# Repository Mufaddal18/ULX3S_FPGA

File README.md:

# ULX3S_FPGA
 University digital Logic Learning Xtensible board with SDRAM

ULX3S FPGA Board, open-source innovation designed to empower education, research, and a myriad of other projects. Standing 8 layer board with the form size of 57x53 mm.

Some of the feature of board are - 

🔹 Affordable Excellence: The ULX3S is low-cost FPGA board packed with all the essential features.

🔹 Versatile and Feature-Packed:  It's an all-in-one solution with an HDMI display, buttons, storage, WiFi connectivity, and compatible connectors. It's designed to be the go-to tool 
   for research, education, and makerspaces.

🔹 Rich Connectivity: With a comprehensive set of chips and connectivity options, including SDRAM, USB, PS/2, SDCARD, Digital Video, FLASH, RTC, I2C, Display, AUDIO, ADC, and more, the 
   ULX3S is a versatile canvas for open-source projects.

At last I would like to thank Emard for making this project open source. 

Your ideas, feedback, and collaboration are not just welcome; they're essential.

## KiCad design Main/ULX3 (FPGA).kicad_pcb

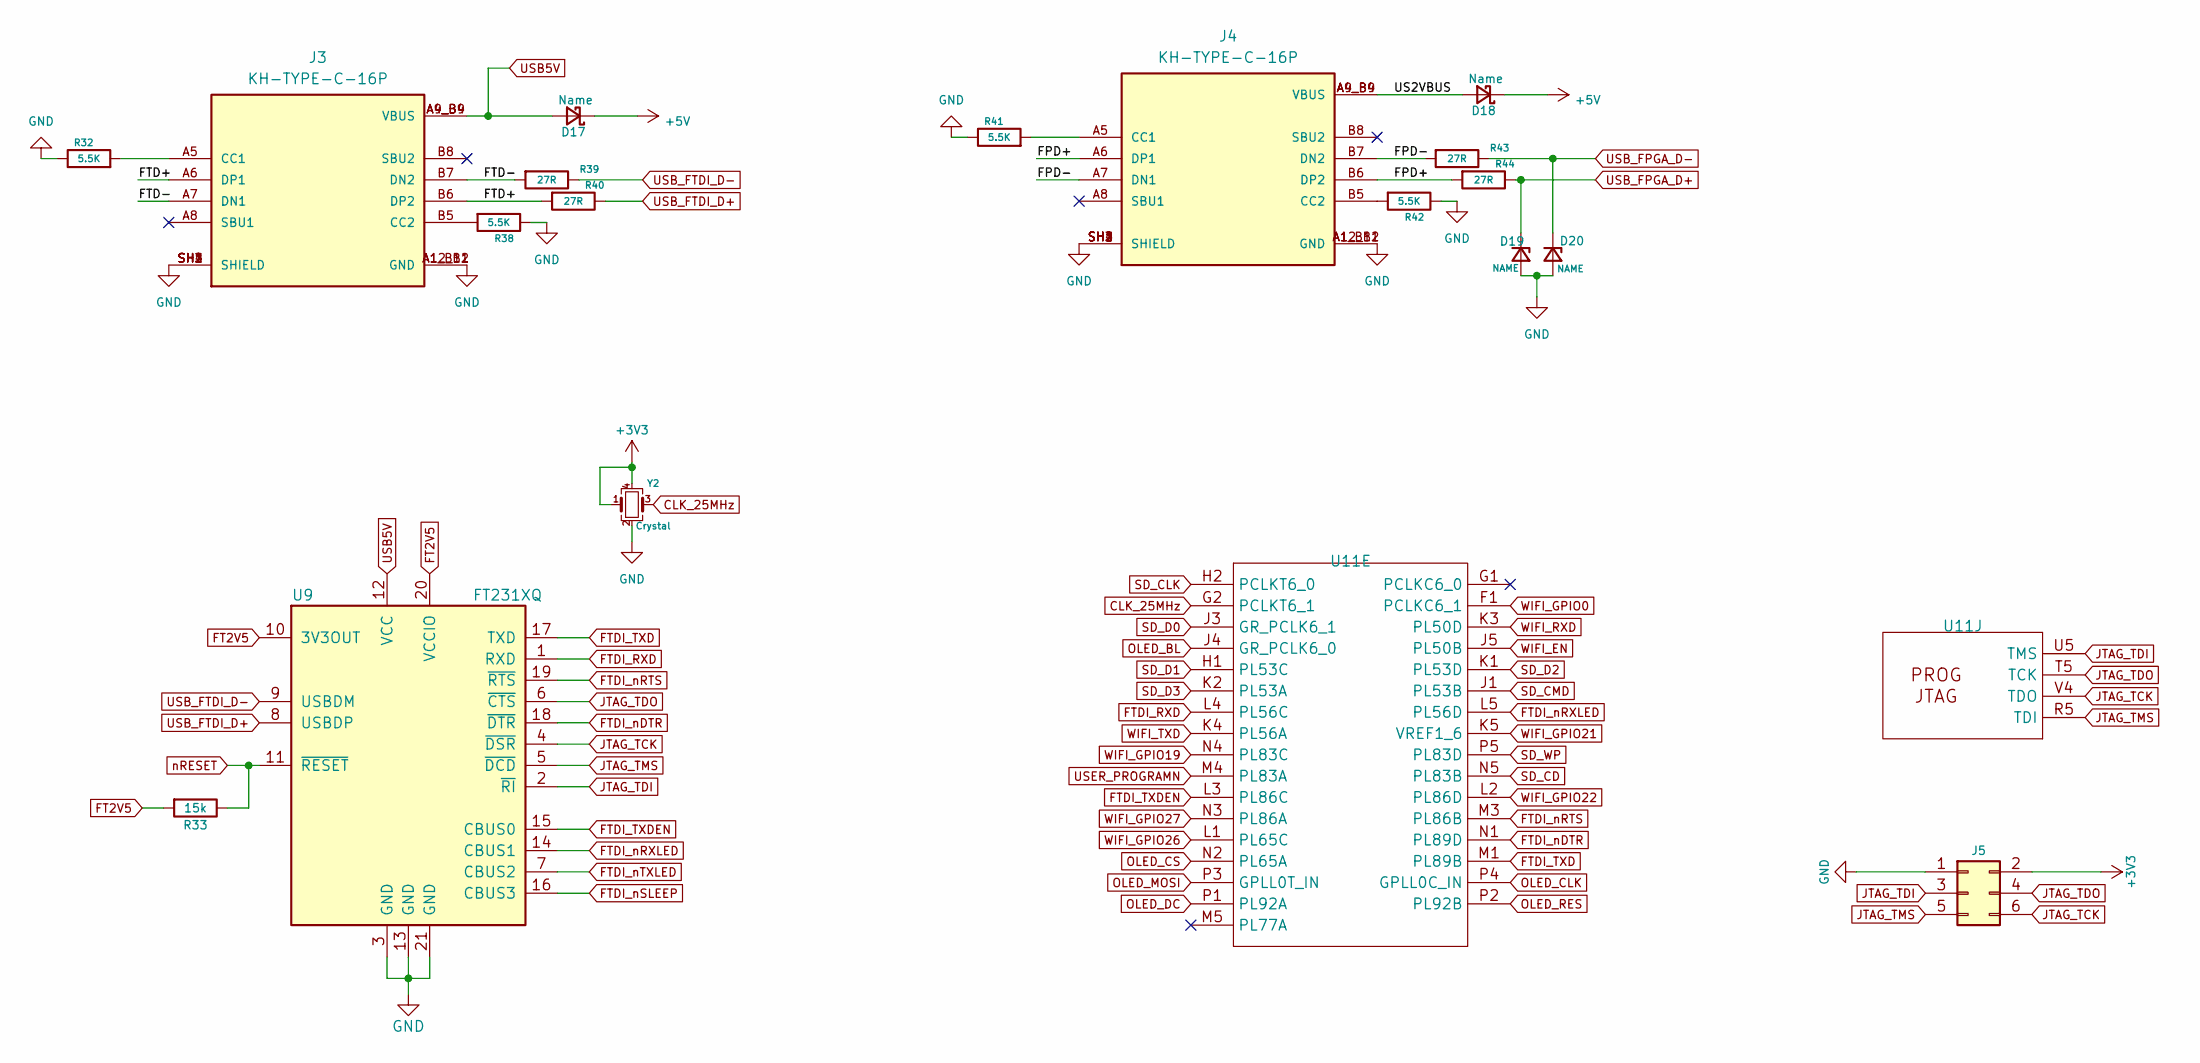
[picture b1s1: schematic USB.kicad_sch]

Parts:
D17, D18: Name; D_0402_1005Metric
D19, D20: NAME; D_0402_1005Metric
J3, J4: KH-TYPE-C-16P; KINGHELM_KH-TYPE-C-16P; PARTREV A0
J5: PinHeader_2x03_P2.54mm_Vertical
R32, R38, R41, R42: 5.5K; R_0402_1005Metric; MPN AC0603JR-0727RL; Mouser 603-AC0603JR-0727RL
R33: 15k; R_0402_1005Metric; MPN RC0603FR-0715KL; Mouser 603-AC0603FR-1015KL
R39, R43: 27R; R_0402_1005Metric; MPN AC0603JR-0727RL; Mouser 603-AC0603JR-0727RL
R40, R44: 27R; R_0402_1005Metric; MPN AC0603JR-0727RL
U9: FT231XQ; MPN FT231XQ; Mouser 895-FT231XQ-R
U11: Latice_LEF5U_FPGA_BGA-381
Y2: Crystal; Crystal_SMD_3225-4Pin_3.2x2.5mm

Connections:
+3V3: J5.2, Y2.1, Y2.4; also elsewhere on the board
+5V: D17.1 (K), D18.1 (K); also elsewhere on the board
/USB/ANT_433MHz: U11.G1 (PCLKC6_0)
/USB/FPD+: J4.A6 (DP1), J4.B6 (DP2), R44.2
/USB/FPD-: J4.A7 (DN1), J4.B7 (DN2), R43.2
/USB/FTD+: J3.A6 (DP1), J3.B6 (DP2), R40.2
/USB/FTD-: J3.A7 (DN1), J3.B7 (DN2), R39.2
/USB/US2VBUS: D18.2 (A), J4.A4_B9 (VBUS), J4.A9_B4 (VBUS)
CLK_25MHz: U11.G2 (PCLKT6_1), Y2.3
FT2V5: R33.2, U9.10 (3V3OUT), U9.20 (VCCIO); also elsewhere on the board
FTDI_RXD: U9.1 (RXD), U11.L4 (PL56C)
FTDI_TXD: U9.17 (TXD), U11.M1 (PL89B)
FTDI_TXDEN: U9.15 (CBUS0), U11.L3 (PL86C)
FTDI_nDTR: U9.18 (~DTR), U11.N1 (PL89D)
FTDI_nRTS: U9.19 (~RTS), U11.M3 (PL86B)
FTDI_nRXLED: U9.14 (CBUS1), U11.L5 (PL56D)
FTDI_nSLEEP: U9.16 (CBUS3); also elsewhere on the board
FTDI_nTXLED: U9.7 (CBUS2); also elsewhere on the board
JTAG_TCK: J5.6, U9.4 (~DSR), U11.V4 (TDO); also elsewhere on the board
JTAG_TDI: J5.3, U9.2 (~RI), U11.U5 (TMS); also elsewhere on the board
JTAG_TDO: J5.4, U9.6 (~CTS), U11.T5 (TCK); also elsewhere on the board
JTAG_TMS: J5.5, U9.5 (~DCD), U11.R5 (TDI); also elsewhere on the board
unnamed: J3.A5 (CC1), R32.2
unnamed: J3.B5 (CC2), R38.2
unnamed: J4.A5 (CC1), R41.2
unnamed: J4.B5 (CC2), R42.2
OLED_BL: U11.J4 (GR_PCLK6_0)
OLED_CLK: U11.P4 (GPLL0C_IN)
OLED_CS: U11.N2 (PL65A)
OLED_DC: U11.P1 (PL92A)
OLED_MOSI: U11.P3 (GPLL0T_IN)
OLED_RES: U11.P2 (PL92B)
SD_CD: U11.N5 (PL83B)
SD_CLK: U11.H2 (PCLKT6_0); also elsewhere on the board
SD_CMD: U11.J1 (PL53B); also elsewhere on the board
SD_D0: U11.J3 (GR_PCLK6_1); also elsewhere on the board
SD_D1: U11.H1 (PL53C); also elsewhere on the board
SD_D2: U11.K1 (PL53D); also elsewhere on the board
SD_D3: U11.K2 (PL53A); also elsewhere on the board
SD_WP: U11.P5 (PL83D)
USB5V: D17.2 (A), J3.A4_B9 (VBUS), J3.A9_B4 (VBUS), U9.12 (VCC)
USB_FPGA_D+: D19.1 (K), R44.1; also elsewhere on the board
USB_FPGA_D-: D20.1 (K), R43.1; also elsewhere on the board
USB_FTDI_D+: R40.1, U9.8 (USBDP)
USB_FTDI_D-: R39.1, U9.9 (USBDM)
USER_PROGRAMN: U11.M4 (PL83A); also elsewhere on the board
WIFI_EN: U11.J5 (PL50B); also elsewhere on the board
WIFI_GPIO0: U11.F1 (PCLKC6_1); also elsewhere on the board
WIFI_GPIO19: U11.N4 (PL83C); also elsewhere on the board
WIFI_GPIO21: U11.K5 (VREF1_6); also elsewhere on the board
WIFI_GPIO22: U11.L2 (PL86D); also elsewhere on the board
WIFI_GPIO26: U11.L1 (PL65C); also elsewhere on the board
WIFI_GPIO27: U11.N3 (PL86A); also elsewhere on the board
WIFI_RXD: U11.K3 (PL50D); also elsewhere on the board
WIFI_TXD: U11.K4 (PL56A); also elsewhere on the board
nRESET: R33.1, U9.11 (~RESET)

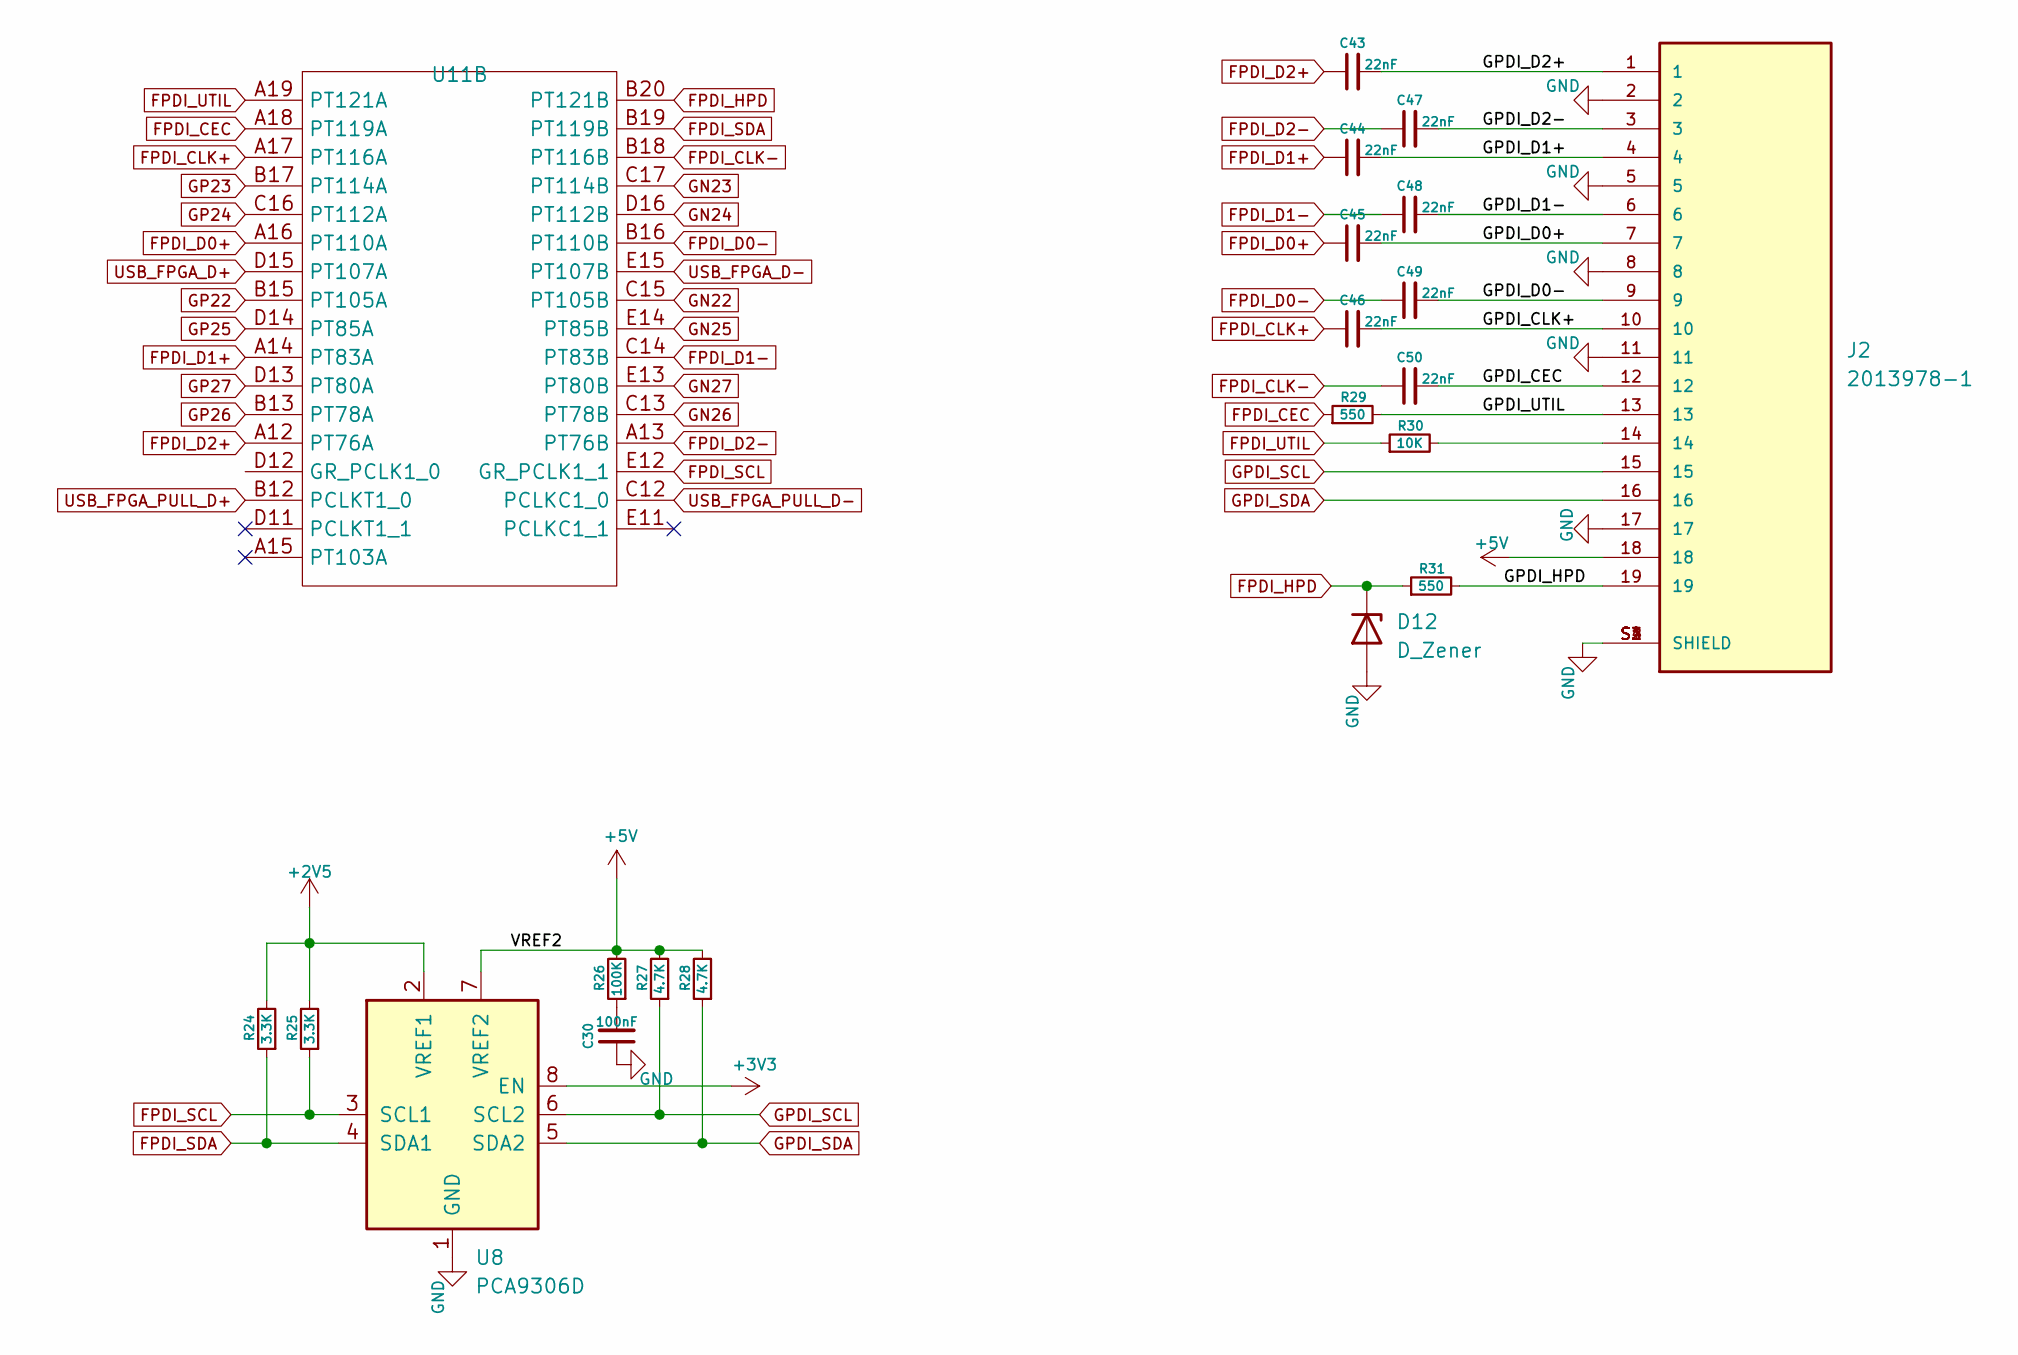
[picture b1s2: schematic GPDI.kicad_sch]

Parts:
C30: 100nF; C_0402_1005Metric
C43, C44, C45, C46, C47, C48, C49, C50: 22nF; C_0402_1005Metric
D12: D_Zener; D_0402_1005Metric
J2: 2013978-1; HDMI-019S
R24, R25: 3.3K; R_0402_1005Metric
R26: 100K; R_0402_1005Metric
R27, R28: 4.7K; R_0402_1005Metric
R29, R31: 550; R_0402_1005Metric
R30: 10K; R_0402_1005Metric
U8: PCA9306D; SO-8_3.9x4.9mm_P1.27mm
U11: Latice_LEF5U_FPGA_BGA-381

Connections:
+2V5: R24.2, R25.2, U8.2 (VREF1); also elsewhere on the board
+3V3: U8.8 (EN); also elsewhere on the board
+5V: J2.18, R26.2, R27.2, R28.2, U8.7 (VREF2); also elsewhere on the board
/GPDI/GPDI_CEC: C50.2, J2.12
/GPDI/GPDI_CLK+: C46.2, J2.10
/GPDI/GPDI_D0+: C45.2, J2.7
/GPDI/GPDI_D0-: C49.2, J2.9
/GPDI/GPDI_D1+: C44.2, J2.4
/GPDI/GPDI_D1-: C48.2, J2.6
/GPDI/GPDI_D2+: C43.2, J2.1
/GPDI/GPDI_D2-: C47.2, J2.3
/GPDI/GPDI_HPD: J2.19, R31.2
/GPDI/GPDI_UTIL: J2.13, R29.2
FPDI_CEC: R29.1, U11.A18 (PT119A)
FPDI_CLK+: C46.1, U11.A17 (PT116A)
FPDI_CLK-: C50.1, U11.B18 (PT116B)
FPDI_D0+: C45.1, U11.A16 (PT110A)
FPDI_D0-: C49.1, U11.B16 (PT110B)
FPDI_D1+: C44.1, U11.A14 (PT83A)
FPDI_D1-: C48.1, U11.C14 (PT83B)
FPDI_D2+: C43.1, U11.A12 (PT76A)
FPDI_D2-: C47.1, U11.A13 (PT76B)
FPDI_HPD: D12.1 (K), R31.1, U11.B20 (PT121B)
FPDI_SCL: R25.1, U8.3 (SCL1), U11.E12 (GR_PCLK1_1); also elsewhere on the board
FPDI_SDA: R24.1, U8.4 (SDA1), U11.B19 (PT119B); also elsewhere on the board
FPDI_UTIL: R30.1, U11.A19 (PT121A)
GN22: U11.C15 (PT105B)
GN23: U11.C17 (PT114B)
GN24: U11.D16 (PT112B)
GN25: U11.E14 (PT85B)
GN26: U11.C13 (PT78B)
GN27: U11.E13 (PT80B)
GP22: U11.B15 (PT105A)
GP23: U11.B17 (PT114A)
GP24: U11.C16 (PT112A)
GP25: U11.D14 (PT85A)
GP26: U11.B13 (PT78A)
GP27: U11.D13 (PT80A)
GPDI_SCL: J2.15, R27.1, U8.6 (SCL2)
GPDI_SDA: J2.16, R28.1, U8.5 (SDA2)
unnamed: C30.2, R26.1
unnamed: J2.14, R30.2
USB_FPGA_D+: U11.D15 (PT107A); also elsewhere on the board
USB_FPGA_D-: U11.E15 (PT107B); also elsewhere on the board
USB_FPGA_PULL_D+: U11.B12 (PCLKT1_0)
USB_FPGA_PULL_D-: U11.C12 (PCLKC1_0)

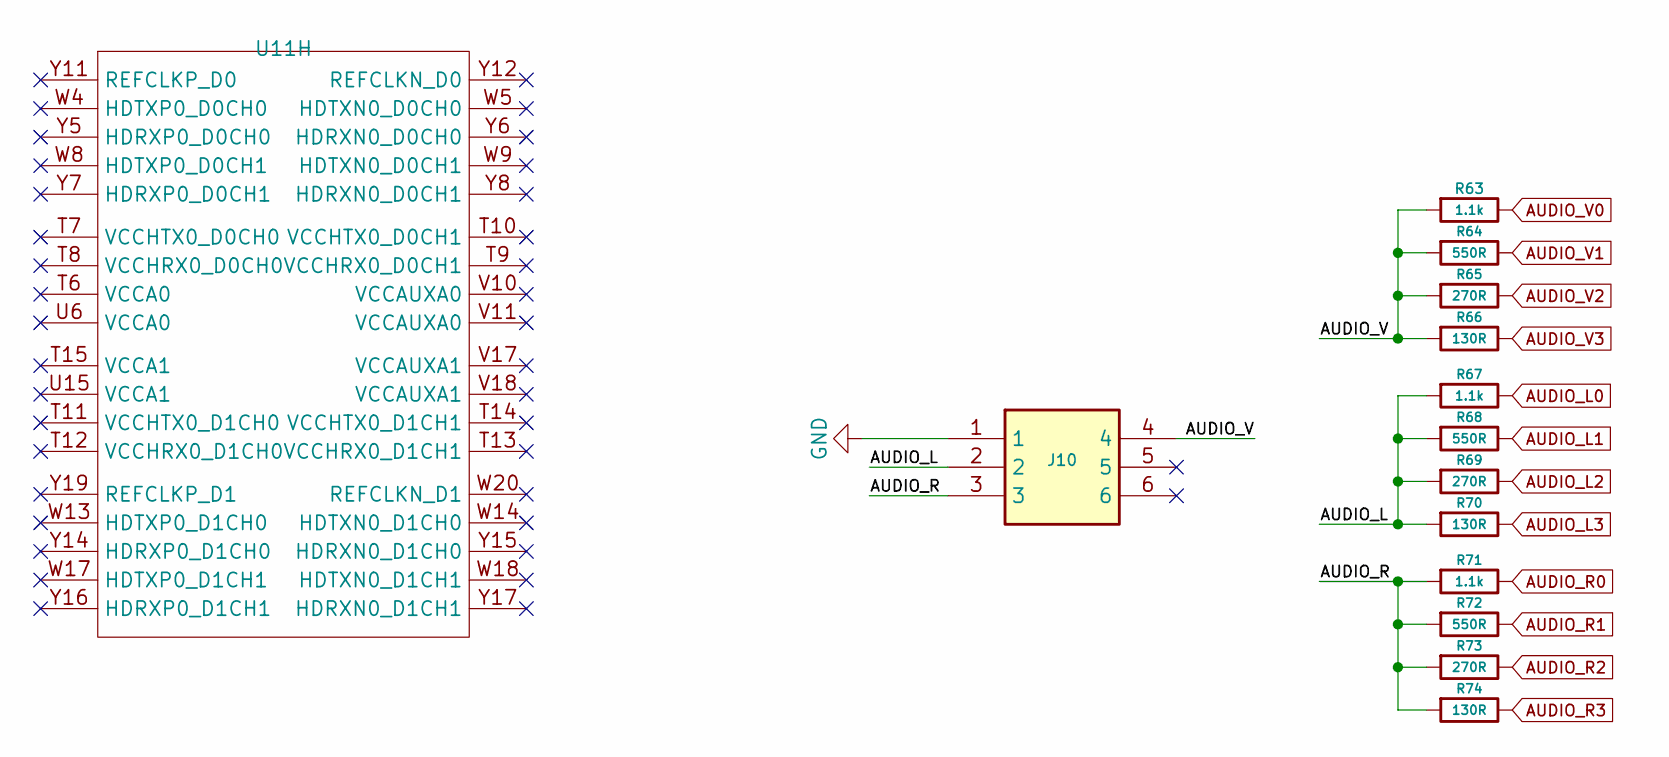
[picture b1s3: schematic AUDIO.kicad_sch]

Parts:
J10: SJ43516SMTTR; Manufacturer_Part_Number SJ-43516-SMT-TR; Mouser Part Number 490-SJ-43516-SMT-TR
R63, R71: 1.1k; R_0402_1005Metric
R64, R72: 550R; R_0402_1005Metric
R65, R73: 270R; R_0402_1005Metric
R66, R74: 130R; R_0402_1005Metric
R67: 1.1k; R_0402_1005Metric; MPN RC0603FR-071K1L; Mouser 603-RC0603FR-071K1L
R68: 550R; R_0402_1005Metric; MPN RC0603FR-07549RL; Mouser 603-RC0603FR-07549RL
R69: 270R; R_0402_1005Metric; MPN RC0603FR-07270RL; Mouser 603-AC0603FR-07270RL
R70: 130R; R_0402_1005Metric; MPN RC0603FR-07130RL; Mouser 603-RC0603FR-07130RL
U11: Latice_LEF5U_FPGA_BGA-381

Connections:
/AUDIO/AUDIO_L: J10.2, R67.2, R68.2, R69.2, R70.2
/AUDIO/AUDIO_R: J10.3, R71.2, R72.2, R73.2, R74.2
/AUDIO/AUDIO_V: J10.4, R63.2, R64.2, R65.2, R66.2
AUDIO_L0: R67.1; also elsewhere on the board
AUDIO_L1: R68.1; also elsewhere on the board
AUDIO_L2: R69.1; also elsewhere on the board
AUDIO_L3: R70.1; also elsewhere on the board
AUDIO_R0: R71.1; also elsewhere on the board
AUDIO_R1: R72.1; also elsewhere on the board
AUDIO_R2: R73.1; also elsewhere on the board
AUDIO_R3: R74.1; also elsewhere on the board
AUDIO_V0: R63.1; also elsewhere on the board
AUDIO_V1: R64.1; also elsewhere on the board
AUDIO_V2: R65.1; also elsewhere on the board
AUDIO_V3: R66.1; also elsewhere on the board

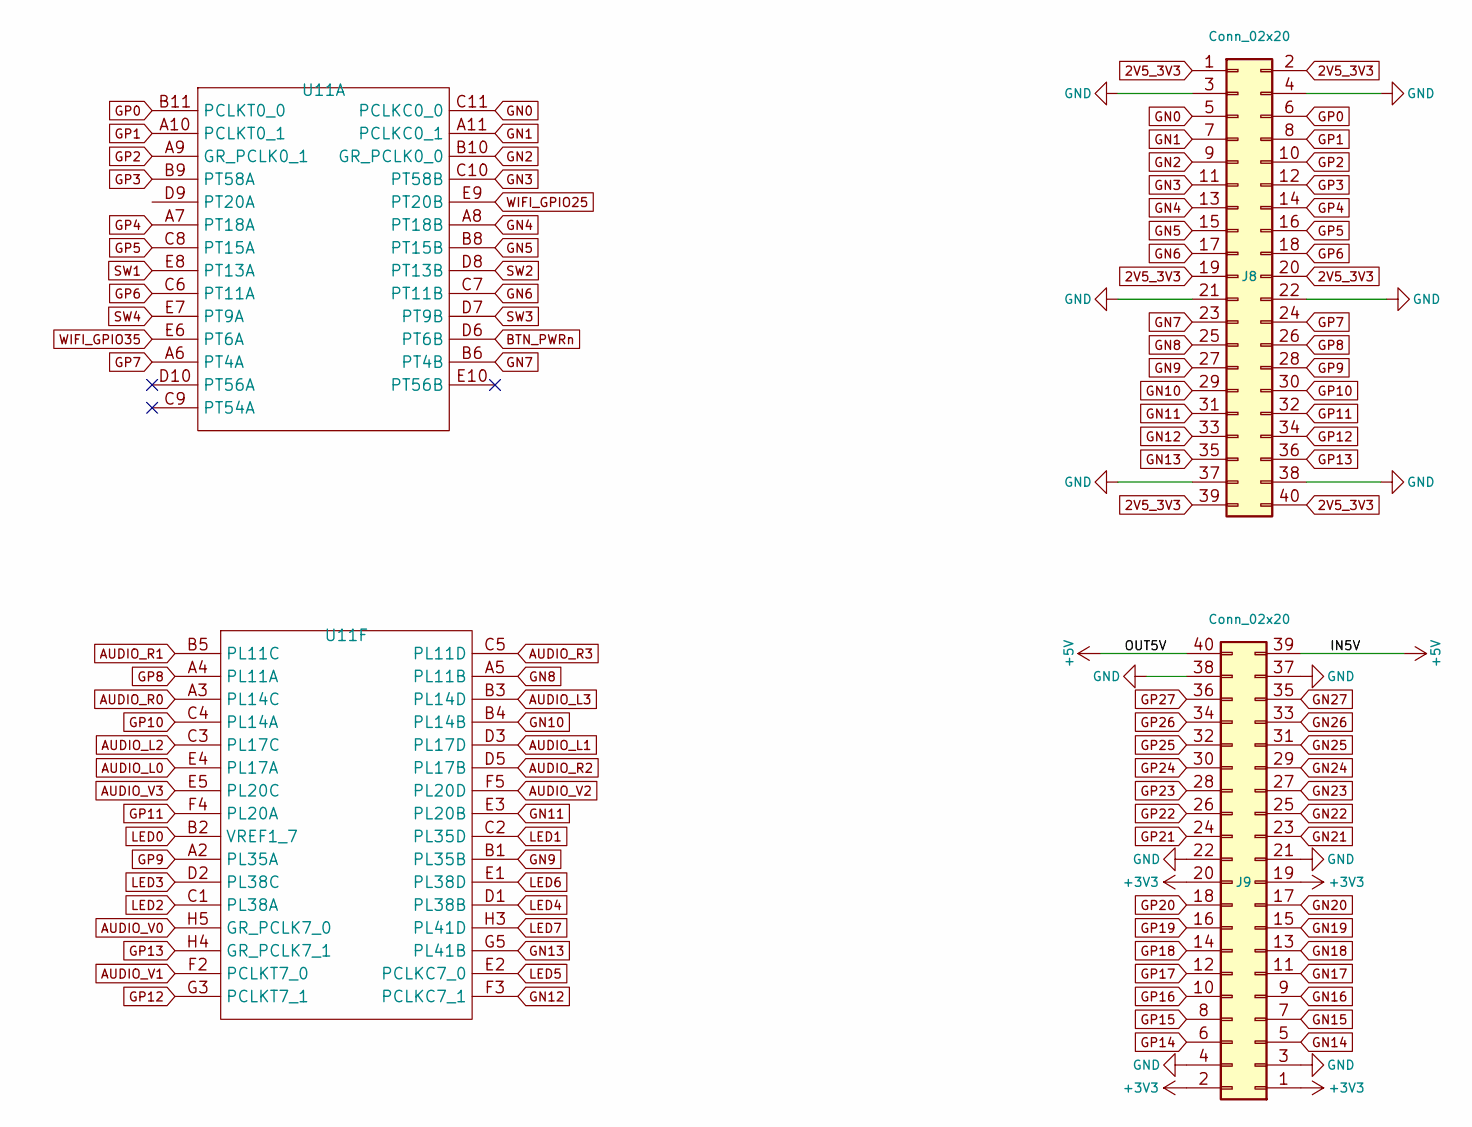
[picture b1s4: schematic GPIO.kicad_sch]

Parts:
J8, J9: Conn_02x20; PinHeader_2x20_P2.54mm_Vertical
U11: Latice_LEF5U_FPGA_BGA-381

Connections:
AUDIO_L0: U11.E4 (PL17A); also elsewhere on the board
AUDIO_L1: U11.D3 (PL17D); also elsewhere on the board
AUDIO_L2: U11.C3 (PL17C); also elsewhere on the board
AUDIO_L3: U11.B3 (PL14D); also elsewhere on the board
AUDIO_R0: U11.A3 (PL14C); also elsewhere on the board
AUDIO_R1: U11.B5 (PL11C); also elsewhere on the board
AUDIO_R2: U11.D5 (PL17B); also elsewhere on the board
AUDIO_R3: U11.C5 (PL11D); also elsewhere on the board
AUDIO_V0: U11.H5 (GR_PCLK7_0); also elsewhere on the board
AUDIO_V1: U11.F2 (PCLKT7_0); also elsewhere on the board
AUDIO_V2: U11.F5 (PL20D); also elsewhere on the board
AUDIO_V3: U11.E5 (PL20C); also elsewhere on the board
BTN_PWRn: U11.D6 (PT6B); also elsewhere on the board
GN0: J8.5, U11.C11 (PCLKC0_0)
GN1: J8.7, U11.A11 (PCLKC0_1)
GN2: J8.9, U11.B10 (GR_PCLK0_0)
GN3: J8.11, U11.C10 (PT58B)
GN4: J8.13, U11.A8 (PT18B)
GN5: J8.15, U11.B8 (PT15B)
GN6: J8.17, U11.C7 (PT11B)
GN7: J8.23, U11.B6 (PT4B)
GN8: J8.25, U11.A5 (PL11B)
GN9: J8.27, U11.B1 (PL35B)
GN10: J8.29, U11.B4 (PL14B)
GN11: J8.31, U11.E3 (PL20B)
GN12: J8.33, U11.F3 (PCLKC7_1); also elsewhere on the board
GN13: J8.35, U11.G5 (PL41B); also elsewhere on the board
GP0: J8.6, U11.B11 (PCLKT0_0)
GP1: J8.8, U11.A10 (PCLKT0_1)
GP2: J8.10, U11.A9 (GR_PCLK0_1)
GP3: J8.12, U11.B9 (PT58A)
GP4: J8.14, U11.A7 (PT18A)
GP5: J8.16, U11.C8 (PT15A)
GP6: J8.18, U11.C6 (PT11A)
GP7: J8.24, U11.A6 (PT4A)
GP8: J8.26, U11.A4 (PL11A)
GP9: J8.28, U11.A2 (PL35A)
GP10: J8.30, U11.C4 (PL14A)
GP11: J8.32, U11.F4 (PL20A)
GP12: J8.34, U11.G3 (PCLKT7_1); also elsewhere on the board
GP13: J8.36, U11.H4 (GR_PCLK7_1); also elsewhere on the board
LED0: U11.B2 (VREF1_7); also elsewhere on the board
LED1: U11.C2 (PL35D); also elsewhere on the board
LED2: U11.C1 (PL38A); also elsewhere on the board
LED3: U11.D2 (PL38C); also elsewhere on the board
LED4: U11.D1 (PL38B); also elsewhere on the board
LED5: U11.E2 (PCLKC7_0); also elsewhere on the board
LED6: U11.E1 (PL38D); also elsewhere on the board
LED7: U11.H3 (PL41D); also elsewhere on the board
unnamed: J8.1, J8.2, J8.19, J8.20, J8.39, J8.40
unnamed: J8.3, J8.4, J8.21, J8.22, J8.37, J8.38, J9.3, J9.4, J9.21, J9.22, J9.37, J9.38
unnamed: J9.1, J9.2, J9.19, J9.20
unnamed: J9.39, J9.40
SW1: U11.E8 (PT13A); also elsewhere on the board
SW2: U11.D8 (PT13B); also elsewhere on the board
SW3: U11.D7 (PT9B); also elsewhere on the board
SW4: U11.E7 (PT9A); also elsewhere on the board
WIFI_GPIO25: U11.E9 (PT20B); also elsewhere on the board
WIFI_GPIO35: U11.E6 (PT6A); also elsewhere on the board

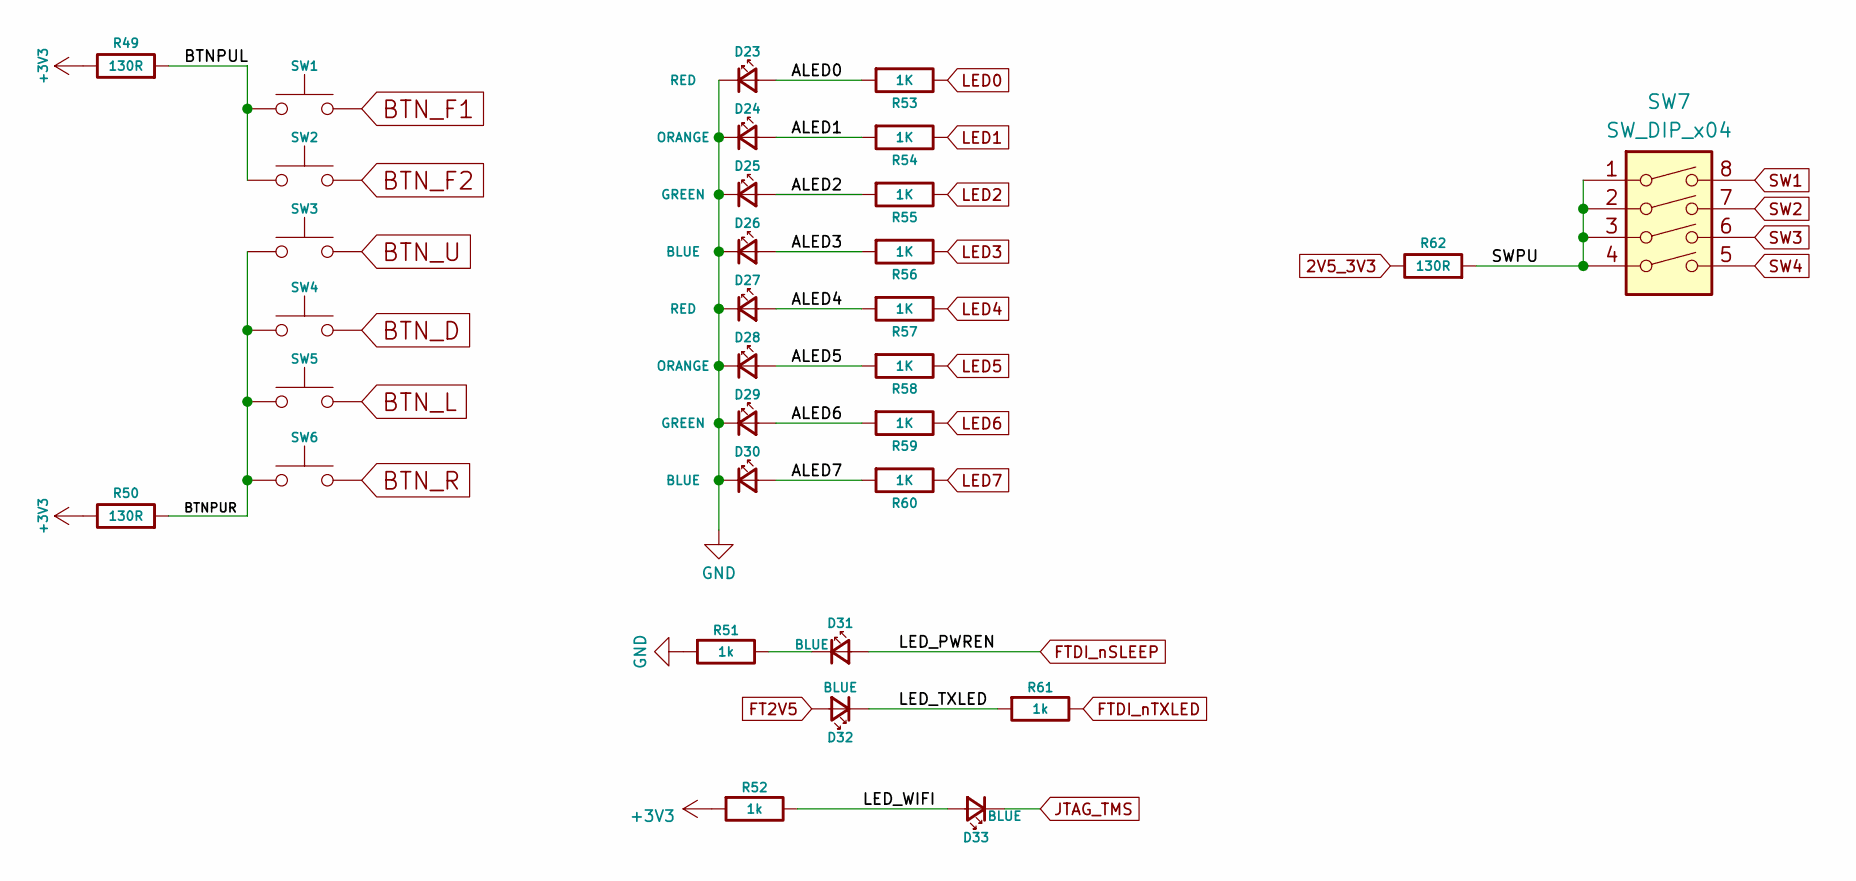
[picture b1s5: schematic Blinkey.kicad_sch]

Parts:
D23, D27: RED; LED_0402_1005Metric
D24, D28: ORANGE; LED_0402_1005Metric
D25, D29: GREEN; LED_0402_1005Metric
D26, D30, D31, D32, D33: BLUE; LED_0402_1005Metric
R49, R50, R62: 130R; R_0402_1005Metric
R51, R52, R61: 1k; R_0402_1005Metric
R53, R54, R55, R56, R57, R58, R59, R60: 1K; R_0402_1005Metric
SW1, SW2, SW3, SW4, SW5, SW6: PTS810SJG250SMTRLFS
SW7: SW_DIP_x04; Switch_4P

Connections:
2V5_3V3: R62.1; also elsewhere on the board
+3V3: R49.1, R50.1, R52.2; also elsewhere on the board
/Blinkey/ALED0: D23.2 (A), R53.2
/Blinkey/ALED1: D24.2 (A), R54.2
/Blinkey/ALED2: D25.2 (A), R55.2
/Blinkey/ALED3: D26.2 (A), R56.2
/Blinkey/ALED4: D27.2 (A), R57.2
/Blinkey/ALED5: D28.2 (A), R58.2
/Blinkey/ALED6: D29.2 (A), R59.2
/Blinkey/ALED7: D30.2 (A), R60.2
/Blinkey/BTNPUR: R50.2, SW3.1, SW3.2 (1), SW4.1, SW4.2 (1), SW5.1, SW5.2 (1), SW6.1, SW6.2 (1)
/Blinkey/LED_TXLED: D32.1 (K), R61.2
/Blinkey/LED_WIFI: D33.2 (A), R52.1
/Blinkey/SWPU: R62.2, SW7.1, SW7.2, SW7.3, SW7.4
BTN_D: SW4.3 (2), SW4.4 (2); also elsewhere on the board
BTN_F2: SW2.3 (2), SW2.4 (2); also elsewhere on the board
BTN_L: SW5.3 (2), SW5.4 (2); also elsewhere on the board
BTN_R: SW6.3 (2), SW6.4 (2); also elsewhere on the board
BTN_U: SW3.3 (2), SW3.4 (2); also elsewhere on the board
FT2V5: D32.2 (A); also elsewhere on the board
FTDI_nSLEEP: D31.2 (A); also elsewhere on the board
FTDI_nTXLED: R61.1; also elsewhere on the board
JTAG_TMS: D33.1 (K); also elsewhere on the board
LED0: R53.1; also elsewhere on the board
LED1: R54.1; also elsewhere on the board
LED2: R55.1; also elsewhere on the board
LED3: R56.1; also elsewhere on the board
LED4: R57.1; also elsewhere on the board
LED5: R58.1; also elsewhere on the board
LED6: R59.1; also elsewhere on the board
LED7: R60.1; also elsewhere on the board
unnamed: D31.1 (K), R51.1
SW1: SW7.8; also elsewhere on the board
SW2: SW7.7; also elsewhere on the board
SW3: SW7.6; also elsewhere on the board
SW4: SW7.5; also elsewhere on the board

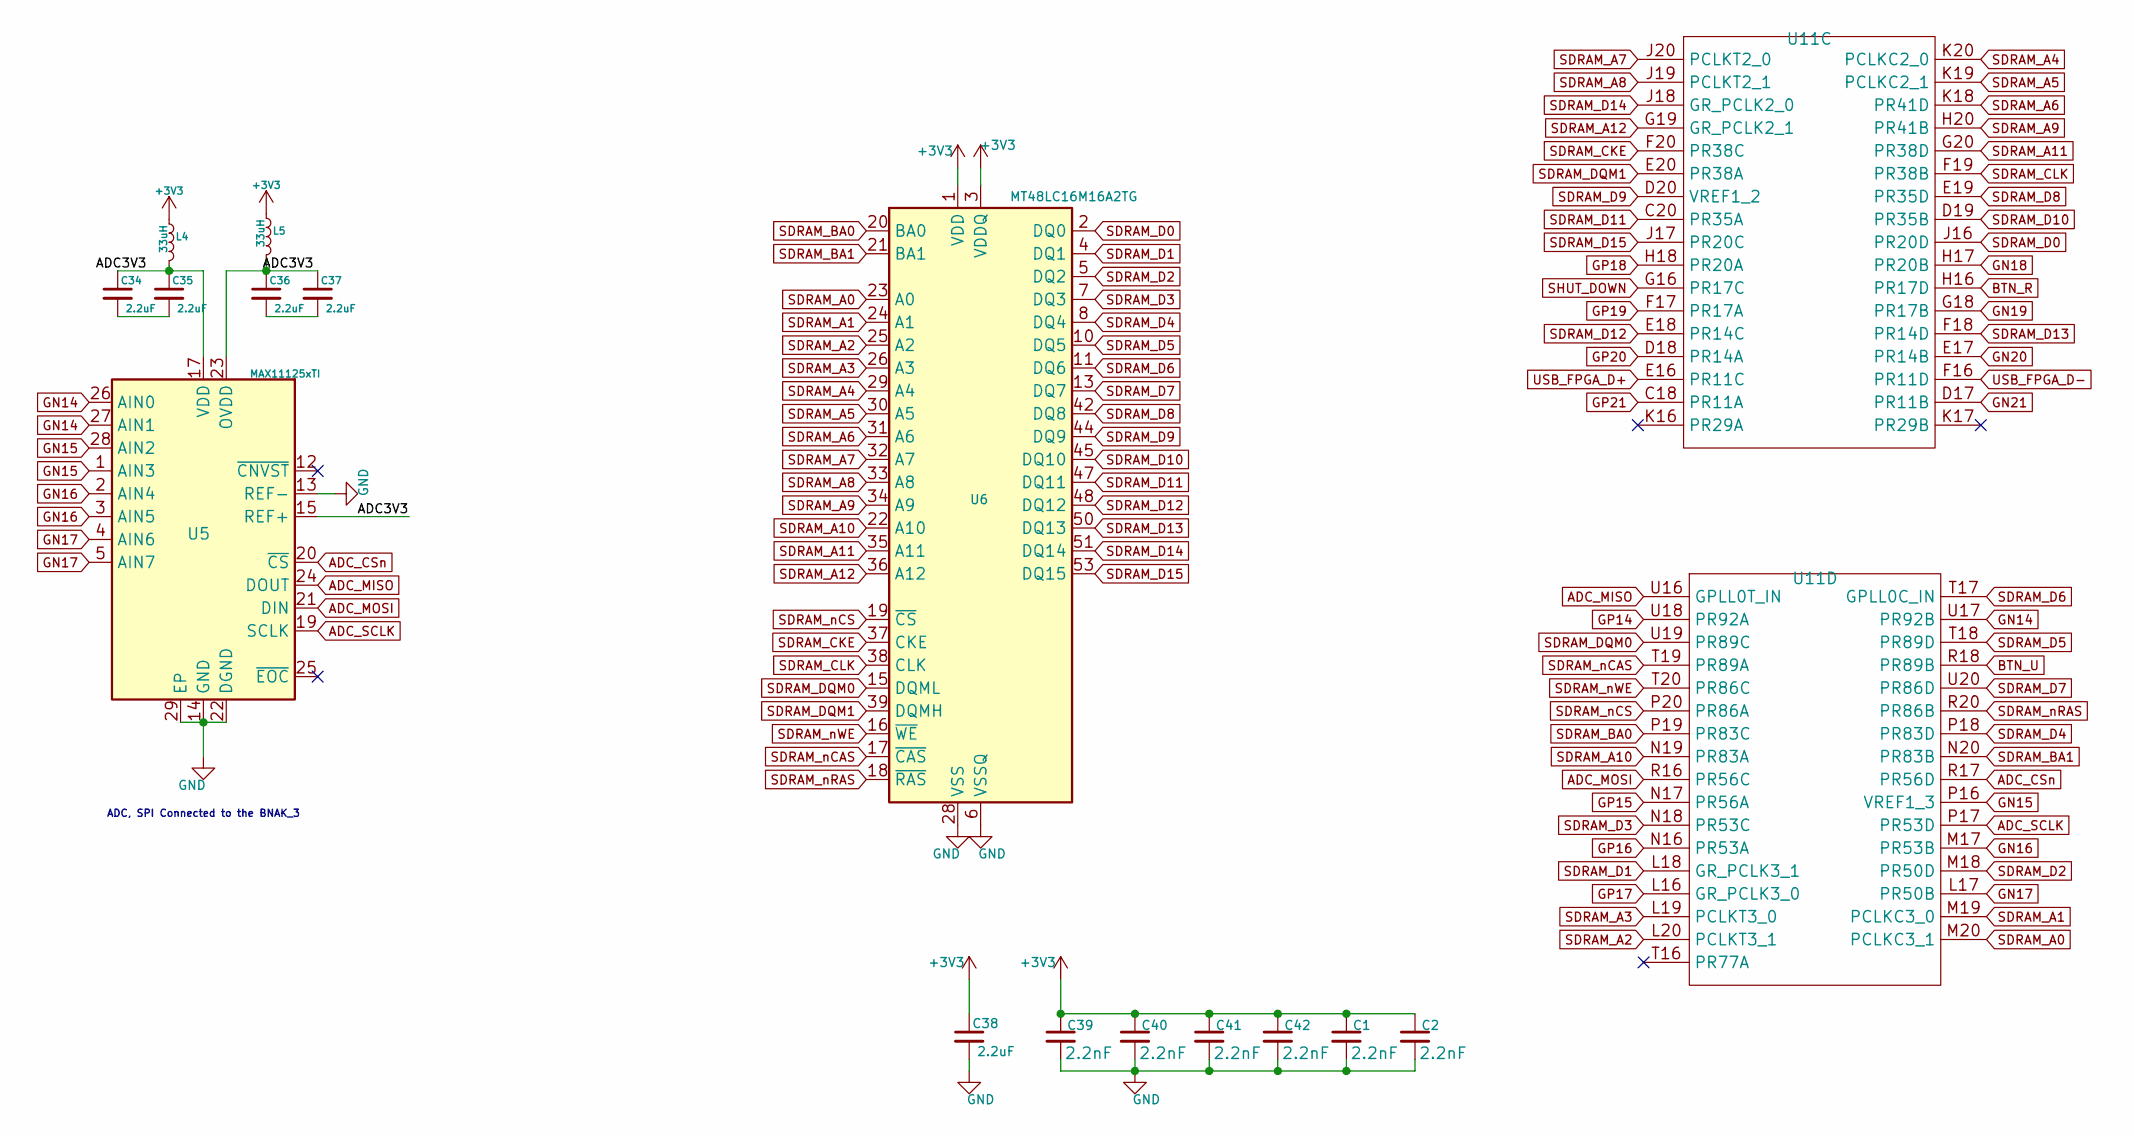
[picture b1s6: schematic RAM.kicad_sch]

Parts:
C1, C2, C39, C40, C41, C42: 2.2nF; C_0402_1005Metric
C34, C35, C36, C37, C38: 2.2uF; C_0402_1005Metric
L4, L5: 33uH; L_0402_1005Metric
U5: MAX11125xTI; TQFN-28-1EP_5x5mm_P0.5mm_EP3.25x3.25mm
U6: MT48LC16M16A2TG; TSOP-II-54_22.2x10.16mm_P0.8mm
U11: Latice_LEF5U_FPGA_BGA-381

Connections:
+3V3: C1.1, C2.1, C38.1, C39.1, C40.1, C41.1, C42.1, L4.1, L5.1, U6.1 (VDD), U6.3 (VDDQ), U6.9 (VDDQ), U6.14 (VDD), U6.27 (VDD), U6.43 (VDDQ), U6.49 (VDDQ); also elsewhere on the board
/RAM/ADC3V3: C34.1, C35.1, C36.1, C37.1, L4.2, L5.2, U5.15 (REF+), U5.17 (VDD), U5.18 (VDD), U5.23 (OVDD)
ADC_CSn: U5.20 (~CS), U11.R17 (PR56D)
ADC_MISO: U5.24 (DOUT), U11.U16 (GPLL0T_IN)
ADC_MOSI: U5.21 (DIN), U11.R16 (PR56C)
ADC_SCLK: U5.19 (SCLK), U11.P17 (PR53D)
BTN_R: U11.H16 (PR17D); also elsewhere on the board
BTN_U: U11.R18 (PR89B); also elsewhere on the board
GN14: U5.26 (AIN0), U5.27 (AIN1), U11.U17 (PR92B)
GN15: U5.1 (AIN3), U5.28 (AIN2), U11.P16 (VREF1_3)
GN16: U5.2 (AIN4), U5.3 (AIN5), U11.M17 (PR53B)
GN17: U5.4 (AIN6), U5.5 (AIN7), U11.L17 (PR50B)
GN18: U11.H17 (PR20B)
GN19: U11.G18 (PR17B)
GN20: U11.E17 (PR14B)
GN21: U11.D17 (PR11B)
GP14: U11.U18 (PR92A)
GP15: U11.N17 (PR56A)
GP16: U11.N16 (PR53A)
GP17: U11.L16 (GR_PCLK3_0)
GP18: U11.H18 (PR20A)
GP19: U11.F17 (PR17A)
GP20: U11.D18 (PR14A)
GP21: U11.C18 (PR11A)
unnamed: C34.2, C35.2
unnamed: C36.2, C37.2
SDRAM_A0: U6.23 (A0), U11.M20 (PCLKC3_1)
SDRAM_A1: U6.24 (A1), U11.M19 (PCLKC3_0)
SDRAM_A2: U6.25 (A2), U11.L20 (PCLKT3_1)
SDRAM_A3: U6.26 (A3), U11.L19 (PCLKT3_0)
SDRAM_A4: U6.29 (A4), U11.K20 (PCLKC2_0)
SDRAM_A5: U6.30 (A5), U11.K19 (PCLKC2_1)
SDRAM_A6: U6.31 (A6), U11.K18 (PR41D)
SDRAM_A7: U6.32 (A7), U11.J20 (PCLKT2_0)
SDRAM_A8: U6.33 (A8), U11.J19 (PCLKT2_1)
SDRAM_A9: U6.34 (A9), U11.H20 (PR41B)
SDRAM_A10: U6.22 (A10), U11.N19 (PR83A)
SDRAM_A11: U6.35 (A11), U11.G20 (PR38D)
SDRAM_A12: U6.36 (A12), U11.G19 (GR_PCLK2_1)
SDRAM_BA0: U6.20 (BA0), U11.P19 (PR83C)
SDRAM_BA1: U6.21 (BA1), U11.N20 (PR83B)
SDRAM_CKE: U6.37 (CKE), U11.F20 (PR38C)
SDRAM_CLK: U6.38 (CLK), U11.F19 (PR38B)
SDRAM_D0: U6.2 (DQ0), U11.J16 (PR20D)
SDRAM_D1: U6.4 (DQ1), U11.L18 (GR_PCLK3_1)
SDRAM_D2: U6.5 (DQ2), U11.M18 (PR50D)
SDRAM_D3: U6.7 (DQ3), U11.N18 (PR53C)
SDRAM_D4: U6.8 (DQ4), U11.P18 (PR83D)
SDRAM_D5: U6.10 (DQ5), U11.T18 (PR89D)
SDRAM_D6: U6.11 (DQ6), U11.T17 (GPLL0C_IN)
SDRAM_D7: U6.13 (DQ7), U11.U20 (PR86D)
SDRAM_D8: U6.42 (DQ8), U11.E19 (PR35D)
SDRAM_D9: U6.44 (DQ9), U11.D20 (VREF1_2)
SDRAM_D10: U6.45 (DQ10), U11.D19 (PR35B)
SDRAM_D11: U6.47 (DQ11), U11.C20 (PR35A)
SDRAM_D12: U6.48 (DQ12), U11.E18 (PR14C)
SDRAM_D13: U6.50 (DQ13), U11.F18 (PR14D)
SDRAM_D14: U6.51 (DQ14), U11.J18 (GR_PCLK2_0)
SDRAM_D15: U6.53 (DQ15), U11.J17 (PR20C)
SDRAM_DQM0: U6.15 (DQML), U11.U19 (PR89C)
SDRAM_DQM1: U6.39 (DQMH), U11.E20 (PR38A)
SDRAM_nCAS: U6.17 (~CAS), U11.T19 (PR89A)
SDRAM_nCS: U6.19 (~CS), U11.P20 (PR86A)
SDRAM_nRAS: U6.18 (~RAS), U11.R20 (PR86B)
SDRAM_nWE: U6.16 (~WE), U11.T20 (PR86C)
SHUT_DOWN: U11.G16 (PR17C)
USB_FPGA_D+: U11.E16 (PR11C); also elsewhere on the board
USB_FPGA_D-: U11.F16 (PR11D); also elsewhere on the board

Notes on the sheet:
ADC, SPI Connected to the BNAK_3
